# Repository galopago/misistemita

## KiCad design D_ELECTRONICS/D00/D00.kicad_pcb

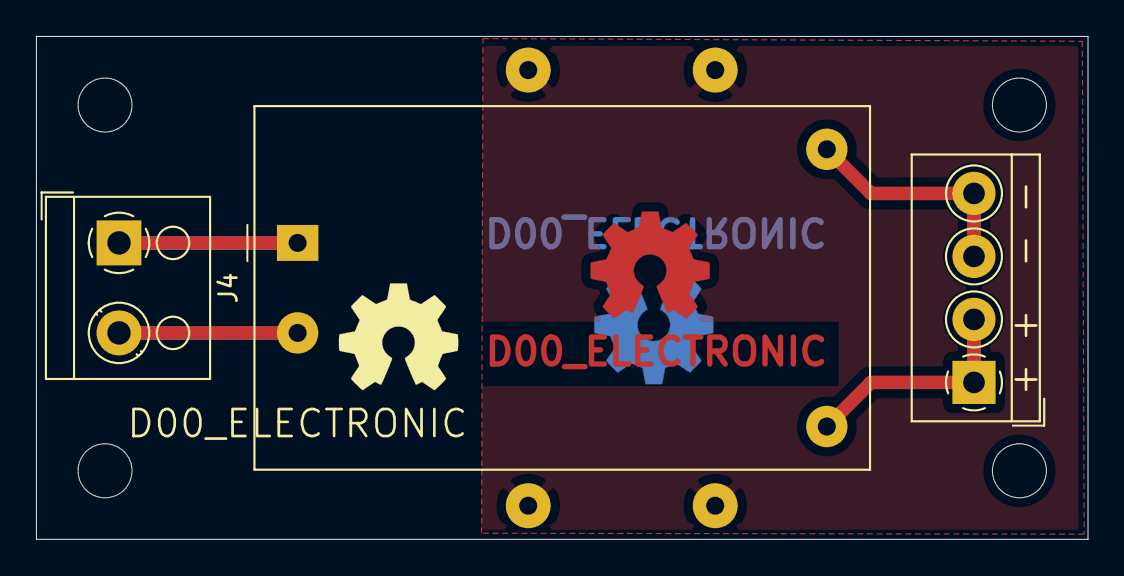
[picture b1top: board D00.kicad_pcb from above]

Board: 2 copper layers, 58.4 x 27.9 mm, 11 parts (0 on the bottom side), 5 nets.

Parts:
HA0, HA5: MountingHole; MountingHole_3mm
HC0, HC5: MountingHole; MountingHole_3mm
J0, J1, J2, J3: Conn_01x01_Male; SolderWirePad_1x01_Drill1mm
J4: Conn_01x02_Female; TerminalBlock_RND_205-00001_1x02_P5.00mm_Horizontal
J5: Conn_01x04_Female; TerminalBlock_4Ucon_1x04_P3.50mm_Horizontal
PS1: HLK-PM03; Converter_ACDC_HiLink_HLK-PMxx

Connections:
unnamed: J0.1, J1.1, J2.1, J3.1
unnamed: J4.1, PS1.1
unnamed: J4.2, PS1.2
unnamed: J5.1, J5.2, PS1.4
unnamed: J5.3, J5.4, PS1.3

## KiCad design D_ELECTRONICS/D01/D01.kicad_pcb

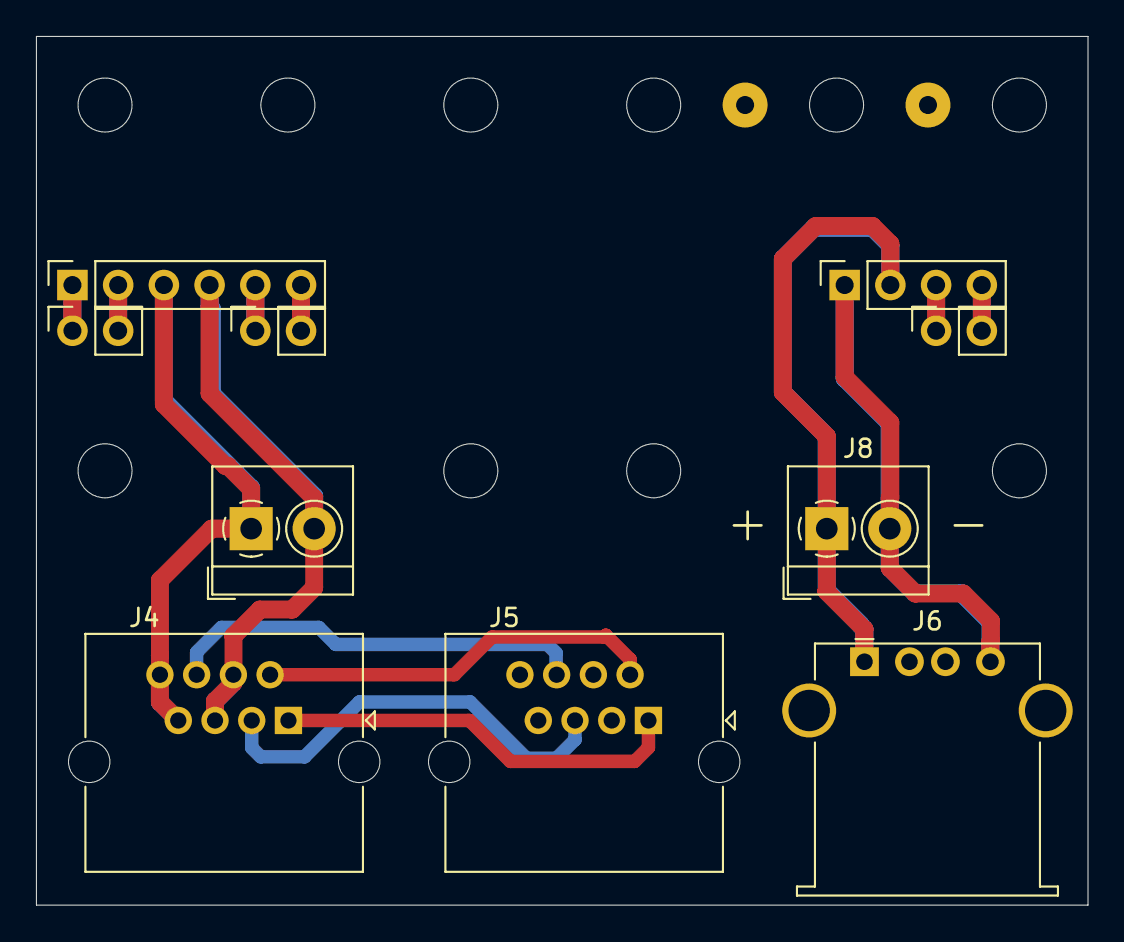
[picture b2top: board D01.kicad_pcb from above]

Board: 2 copper layers, 58.4 x 48.3 mm, 22 parts (0 on the bottom side), 15 nets.

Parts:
HA0, HA1, HA2, HA3, HA4, HA5: MountingHole; MountingHole_3mm
HC0, HC2, HC3, HC5: MountingHole; MountingHole_3mm
J0, J1: Conn_01x01_Male; SolderWirePad_1x01_Drill1mm
J2, J3, J11: Conn_01x02_Female; PinSocket_1x02_P2.54mm_Vertical
J4, J5: RJ45; RJ45_Wayconn_MJEA-880X1_Horizontal
J6: USB_A; USB_A_Stewart_SS-52100-001_Horizontal
J7, J8: Conn_01x02_Female; TerminalBlock_4Ucon_1x02_P3.50mm_Horizontal
J9: Conn_01x04_Female; PinSocket_1x04_P2.54mm_Vertical
J10: Conn_01x06_Female; PinSocket_1x06_P2.54mm_Vertical

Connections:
unnamed: J0.1, J1.1
unnamed: J4.1, J5.1
unnamed: J4.2, J5.2
unnamed: J4.3, J5.5
unnamed: J4.6, J5.6
unnamed: J6.1, J8.1, J9.2
unnamed: J6.4, J8.2, J9.1
unnamed: J2.1, J10.1
unnamed: J2.2, J10.2
unnamed: J4.7, J4.8, J7.1, J10.3
unnamed: J4.4, J4.5, J7.2, J10.4
unnamed: J3.1, J10.5
unnamed: J3.2, J10.6
unnamed: J9.3, J11.1
unnamed: J9.4, J11.2

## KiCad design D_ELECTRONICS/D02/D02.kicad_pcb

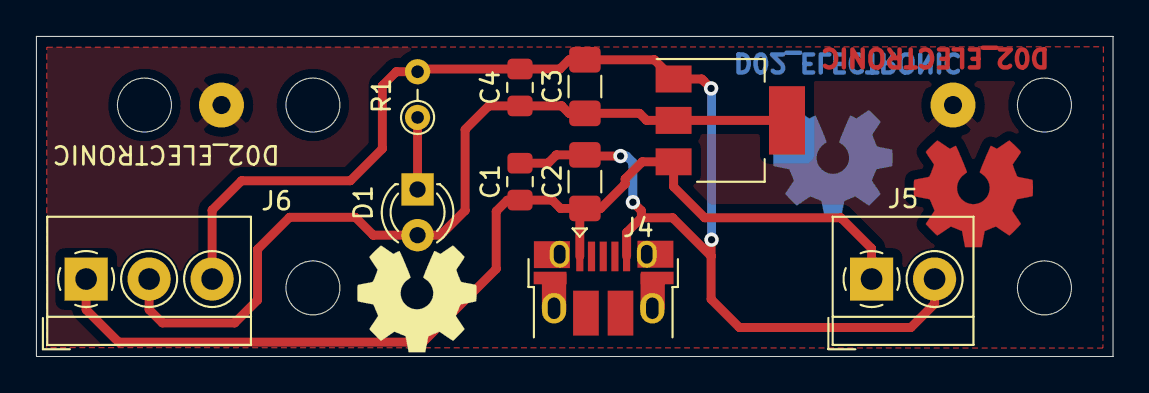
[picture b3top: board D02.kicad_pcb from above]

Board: 2 copper layers, 59.8 x 17.8 mm, 17 parts (0 on the bottom side), 5 nets.

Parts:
C1, C4: C; C_0805_2012Metric_Pad1.15x1.40mm_HandSolder
C2, C3: C; C_1206_3216Metric_Pad1.42x1.75mm_HandSolder
D1: LED; LED_D3.0mm
HA0, HA1, HA5: MountingHole; MountingHole_3mm
HB0, HB5: MountingHole; MountingHole_3mm
J0, J1: Conn_01x01_Male; SolderWirePad_1x01_Drill1mm
J4: USB_B_Micro; USB_Micro-B_Amphenol_10103594-0001LF_Horizontal
J5: Conn_01x02_Female; TerminalBlock_4Ucon_1x02_P3.50mm_Horizontal
J6: Conn_01x03_Female; TerminalBlock_4Ucon_1x03_P3.50mm_Horizontal
R1: R; R_Axial_DIN0204_L3.6mm_D1.6mm_P2.54mm_Vertical
U1: AMS1117-3.3; SOT-223-3_TabPin2

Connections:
unnamed: C1.1, C2.1, J4.1, J5.1, J6.1, U1.3
unnamed: C1.2, C2.2, C3.2, C4.2, J4.5, J5.2, J6.3, R1.2, U1.1
unnamed: C3.1, C4.1, D1.2, J6.2, U1.2
unnamed: D1.1, R1.1
unnamed: J0.1, J1.1

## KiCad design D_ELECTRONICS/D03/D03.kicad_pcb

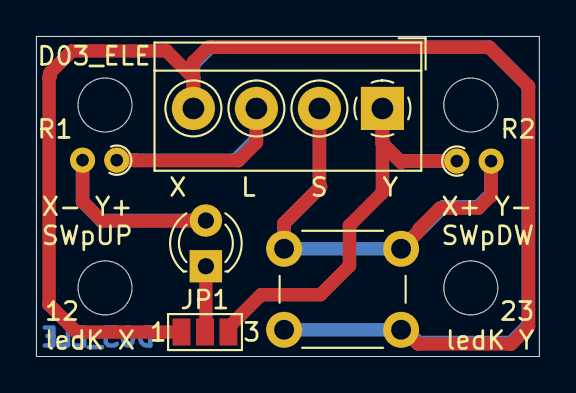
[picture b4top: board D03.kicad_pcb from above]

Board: 2 copper layers, 27.9 x 17.8 mm, 10 parts (0 on the bottom side), 6 nets.

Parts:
D1: LED; LED_D3.0mm
HA0, HA2: MountingHole; MountingHole_3mm
HB0, HB2: MountingHole; MountingHole_3mm
J4: Conn_01x04_Female; TerminalBlock_4Ucon_1x04_P3.50mm_Horizontal
JP1: SolderJumper_3_Open; SolderJumper-3_P1.3mm_Open_Pad1.0x1.5mm_NumberLabels
R1, R2: R; R_Axial_DIN0204_L3.6mm_D1.6mm_P1.90mm_Vertical
SW1: SW_Push; SW_PUSH_6mm

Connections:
unnamed: D1.1, JP1.2
unnamed: D1.2, R1.2
unnamed: J4.1, JP1.3, R2.1
unnamed: J4.2, R2.2, SW1.2
unnamed: J4.3, R1.1
unnamed: J4.4, JP1.1, SW1.1

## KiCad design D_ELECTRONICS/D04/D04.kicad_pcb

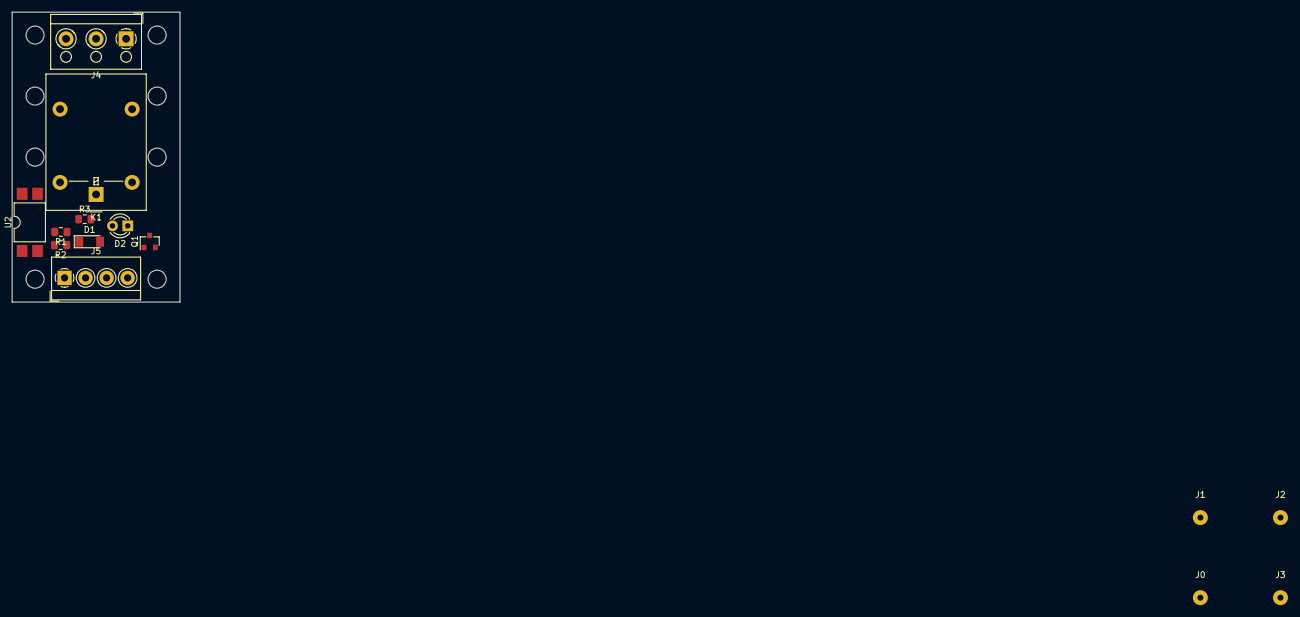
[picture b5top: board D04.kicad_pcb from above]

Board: 2 copper layers, 27.9 x 48.3 mm, 22 parts (0 on the bottom side), 11 nets, no tracks yet.

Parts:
D1: LL4148; D_MiniMELF
D2: LED; LED_D3.0mm
HA0, HA2: MountingHole; MountingHole_3mm
HB0, HB2: MountingHole; MountingHole_3mm
HC0, HC2: MountingHole; MountingHole_3mm
HE0, HE2: MountingHole; MountingHole_3mm
J0, J1, J2, J3: Conn_01x01_Male; SolderWirePad_1x01_Drill1mm
J4: Conn_01x03_Female; TerminalBlock_RND_205-00002_1x03_P5.00mm_Horizontal
J5: Conn_01x04_Female; TerminalBlock_4Ucon_1x04_P3.50mm_Horizontal
K1: G5LE-1; Relay_SPDT_Omron-G5LE-1
Q1: MMBT3904; SOT-23
R1, R2, R3: R; R_0805_2012Metric_Pad1.15x1.40mm_HandSolder
U2: LTV-817S; SMDIP-4_W9.53mm

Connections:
unnamed: D1.1, J5.1, K1.5, R3.1, U2.4
unnamed: D1.2, D2.1, K1.2, Q1.3
unnamed: D2.2, R3.2
unnamed: J0.1, J1.1, J2.1, J3.1
unnamed: J4.1, K1.3
unnamed: J4.2, K1.1
unnamed: J4.3, K1.4
unnamed: J5.4, Q1.2
unnamed: Q1.1, R1.1
unnamed: R1.2, U2.3
unnamed: R2.2, U2.1

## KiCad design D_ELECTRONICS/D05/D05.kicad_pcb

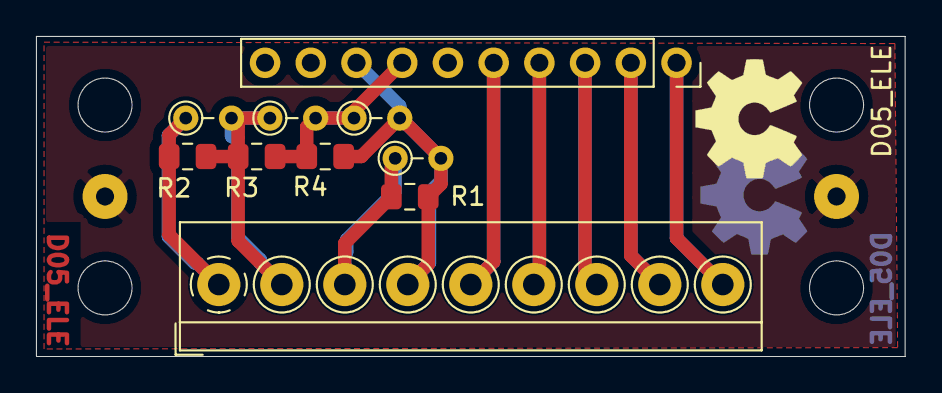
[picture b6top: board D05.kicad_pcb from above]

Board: 2 copper layers, 48.3 x 17.8 mm, 16 parts (0 on the bottom side), 11 nets.

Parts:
HA0, HA4: MountingHole; MountingHole_3mm
HB0, HB4: MountingHole; MountingHole_3mm
J0, J1: Conn_01x01_Male; SolderWirePad_1x01_Drill1mm
J4: Conn_01x10_Female; PinSocket_1x10_P2.54mm_Vertical
J5: Conn_01x09_Female; TerminalBlock_4Ucon_1x09_P3.50mm_Horizontal
R1, R2, R3, R4: R; R_Axial_DIN0204_L3.6mm_D1.6mm_P2.54mm_Vertical
R11, R22, R33, R44: R; R_0805_2012Metric_Pad1.15x1.40mm_HandSolder

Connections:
unnamed: J0.1, J1.1
unnamed: J4.1, J5.9
unnamed: J4.2, J5.8
unnamed: J4.3, J5.7
unnamed: J4.4, J5.6
unnamed: J4.5, J5.5
unnamed: J4.7, R3.2, R4.1, R33.2, R44.1
unnamed: J4.8, J5.4, R1.2, R4.2, R11.2, R44.2
unnamed: J5.1, R2.1, R22.1
unnamed: J5.2, R2.2, R3.1, R22.2, R33.1
unnamed: J5.3, R1.1, R11.1

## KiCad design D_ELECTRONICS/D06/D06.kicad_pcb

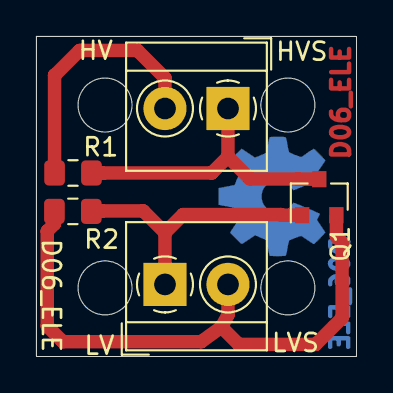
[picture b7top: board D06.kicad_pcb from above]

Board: 2 copper layers, 17.8 x 17.8 mm, 9 parts (0 on the bottom side), 4 nets.

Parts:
HA0, HA1: MountingHole; MountingHole_3mm
HB0, HB1: MountingHole; MountingHole_3mm
J4, J5: Conn_01x02_Female; TerminalBlock_4Ucon_1x02_P3.50mm_Horizontal
Q1: BSS138; SOT-23
R1, R2: R; R_0805_2012Metric_Pad1.15x1.40mm_HandSolder

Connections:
unnamed: J4.1, Q1.1, R2.1
unnamed: J4.2, Q1.2, R2.2
unnamed: J5.1, Q1.3, R1.2
unnamed: J5.2, R1.1
